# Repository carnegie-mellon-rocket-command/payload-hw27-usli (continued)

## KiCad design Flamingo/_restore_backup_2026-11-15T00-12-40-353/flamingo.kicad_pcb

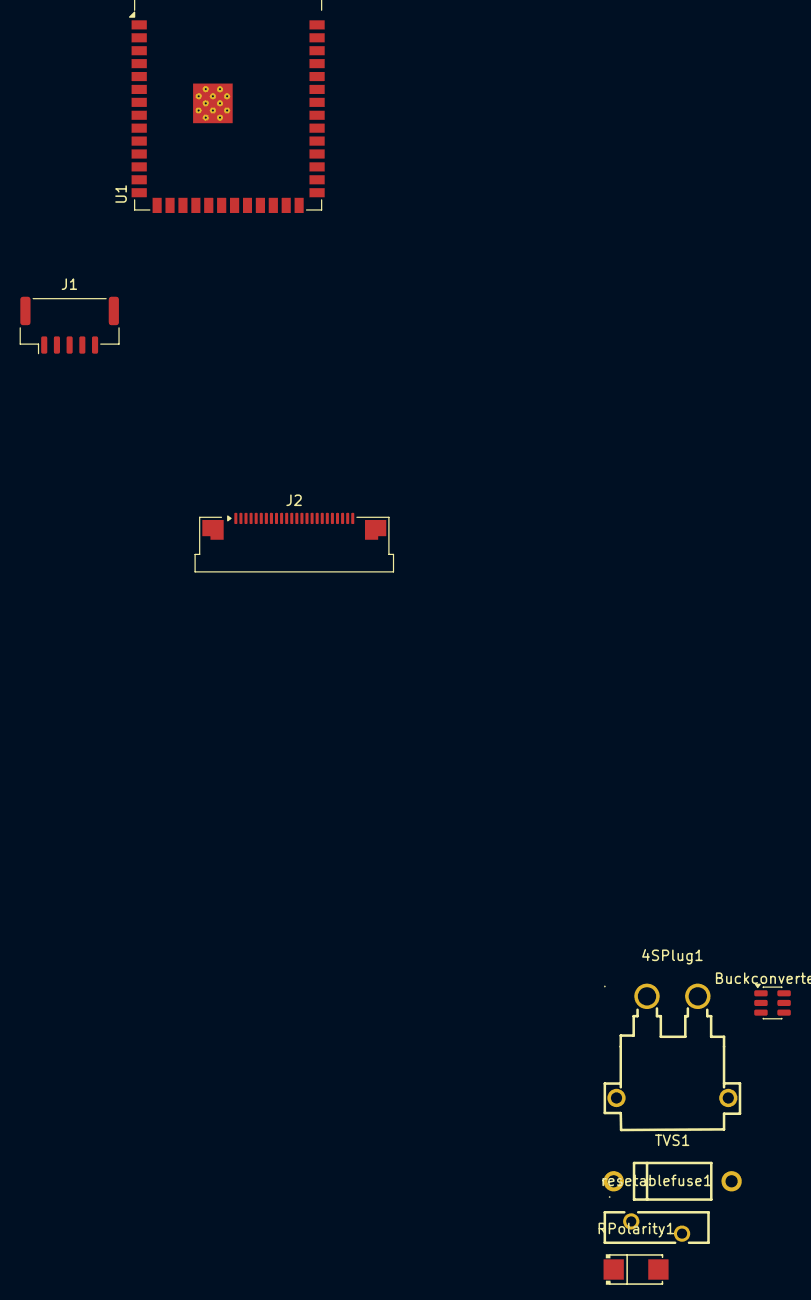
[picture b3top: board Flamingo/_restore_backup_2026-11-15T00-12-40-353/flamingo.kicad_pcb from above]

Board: 2 copper layers, 8 parts (0 on the bottom side), 22 nets, no tracks yet.

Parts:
4SPlug1: XT30PW-M; CONN-TH_XT30PW-M
Buckconverter1: TPS54302DDCR; SOT-23-6
J1: STA-M020X; JST_GH_BM05B-GHS-TBT_1x05-1MP_P1.25mm_Vertical
J2: Conn_01x24; Amphenol_F32Q-1A7x1-11024_1x24-1MP_P0.5mm_Horizontal
RPolarity1: SS34_C8678; SMA_L4.3-W2.6-LS5.2-RD
TVS1: P6KE20A_C499762; DO-15_BD3.1-L6.7-P10.70-D0.9-RD
U1: ESP32-S3-WROOM-1-N16R8; ESP32-S3-WROOM-1
resetablefuse1: MF-R160; FUSE-TH_L10.2-W3.0-P5.10-D0.8-S1.20

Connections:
/ESP32-S3 core/CAM_HREF: J2.9, U1.18 (IO10)
/ESP32-S3 core/CAM_PCLK: J2.17, U1.16 (IO46)
/ESP32-S3 core/CAM_RST: J2.6, U1.6 (IO6)
/ESP32-S3 core/CAM_SCL: J2.5, U1.5 (IO5)
/ESP32-S3 core/CAM_SDA: J2.3, U1.4 (IO4)
/ESP32-S3 core/CAM_VSYNC: J2.7, U1.17 (IO9)
/ESP32-S3 core/CAM_XCLK: J2.13, U1.21 (IO13)
/ESP32-S3 core/CAM_Y2: J2.19, U1.8 (IO15)
/ESP32-S3 core/CAM_Y3: J2.21, U1.9 (IO16)
/ESP32-S3 core/CAM_Y4: J2.22, U1.10 (IO17)
/ESP32-S3 core/CAM_Y5: J2.20, U1.11 (IO18)
/ESP32-S3 core/CAM_Y6: J2.18, U1.12 (IO8)
/ESP32-S3 core/CAM_Y7: J2.16, U1.13 (USB_D-)
/ESP32-S3 core/CAM_Y8: J2.14, U1.14 (USB_D+)
/ESP32-S3 core/CAM_Y9: J2.12, U1.15 (IO3)
/ESP32-S3 core/LASER_RX: J1.4, U1.38 (IO2)
/ESP32-S3 core/LASER_TX: J1.3, U1.39 (IO1)
/Power/Input Protection/Protected out: Buckconverter1.3 (VIN), RPolarity1.1 (K), TVS1.1 (C)
/Power/Input Protection/Unprotected In: 4SPlug1.2 (+), resetablefuse1.1
GND: 4SPlug1.1 (-), Buckconverter1.1 (GND), J1.1, J2.15, TVS1.2 (A)
unnamed: RPolarity1.2 (A), resetablefuse1.2
unnamed: U1.1 (GND), U1.40 (GND), U1.41 (GND)
